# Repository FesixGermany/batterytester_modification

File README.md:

# batterytester_modification  

Own design to replace the PCB and the support material of a commercially available battery tester.  
The main PCB is made from 1.5mm FR4 material, the support underneath is 2mm FR4.  
The fixed probe PCB was desoldered and reused, the sliding probe assembly was also reused.  
All tested with 30A current, no excessive heat detected with thermal camera.  
  
Changes made compared to original tester:  
- Slots for sliding probe elongated to accept at least a 18650 comfortably and also button cells  
- Wider traces for higher testing current  
- Longer cables for sliding probe  
- Four big holes added to accept 4mm plugs  
  
KiCAD 3D render of PCB:  

Original tester:  

Own version with reused parts:

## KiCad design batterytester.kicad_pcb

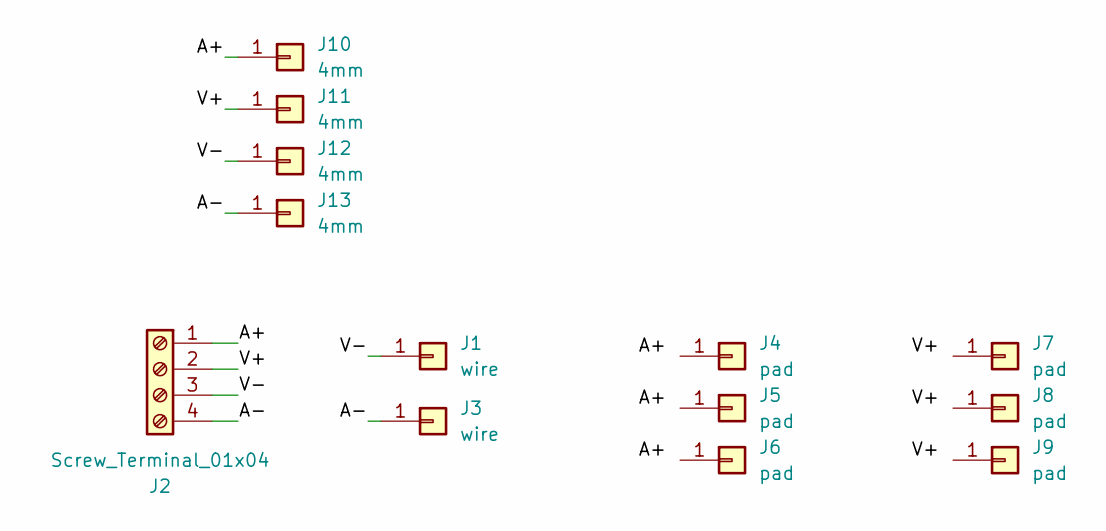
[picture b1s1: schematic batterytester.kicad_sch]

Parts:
J1, J3: wire; SolderWire-2.5sqmm_1x01_D2.4mm_OD3.6mm
J2: Screw_Terminal_01x04; TerminalBlock_Phoenix_MKDS-1,5-4_1x04_P5.00mm_Horizontal
J4, J5, J6, J7, J8, J9: pad; SolderWirePad_1x01_SMD_5x10mm
J10, J11, J12, J13: 4mm; SolderWire-2sqmm_1x01_D2mm_OD3.9mm

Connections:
/A+: J2.1, J4.1, J5.1, J6.1, J10.1
/A-: J2.4, J3.1, J13.1
/V+: J2.2, J7.1, J8.1, J9.1, J11.1
/V-: J1.1, J2.3, J12.1

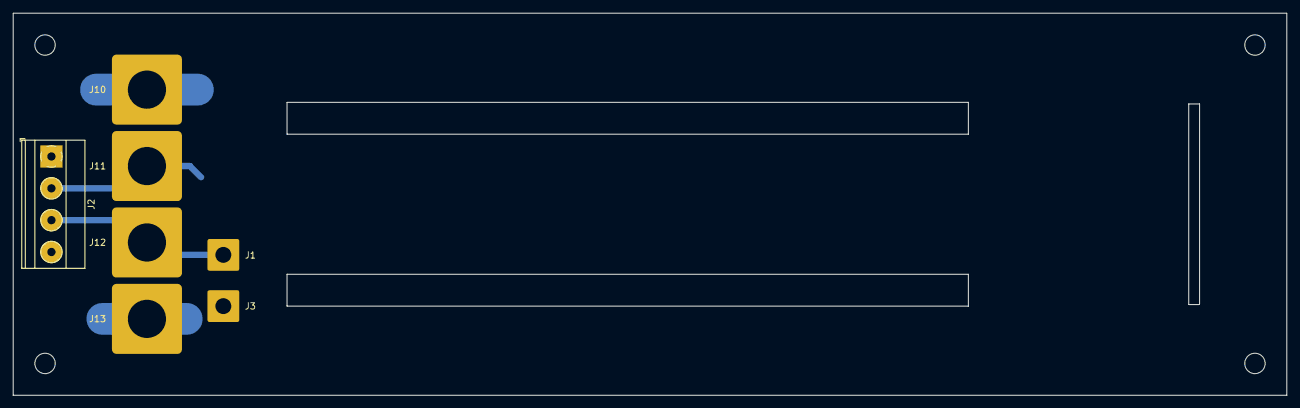
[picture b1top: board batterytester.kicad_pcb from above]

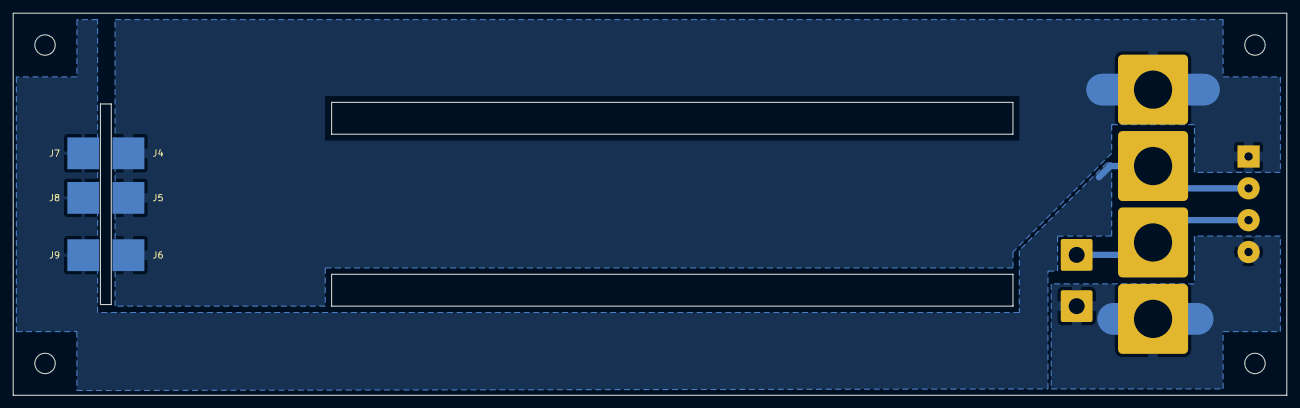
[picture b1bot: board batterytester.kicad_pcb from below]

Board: 2 copper layers, 200.0 x 60.0 mm, 13 parts (6 on the bottom side), 4 nets.

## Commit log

2024-01-08 Full project
2024-01-08 Additional info in readme
